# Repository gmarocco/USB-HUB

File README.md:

# USB Hub · microSD Reader · USB-UART — V2

A compact USB 2.0 Hi-Speed expansion board. A single USB Type-C upstream connection provides **four USB Type-A ports**, a **microSD card reader** and a **USB-to-UART bridge** with a 10-pin header. Everything fits on a 90 × 55 mm four-layer PCB designed in KiCad 10.

## Features

- **USB Type-C upstream port**: USB 2.0, reversible, with 5.1 kΩ pull-downs on CC1/CC2 so any USB-C host or charger turns on VBUS
- **Two cascaded Microchip USB2514B hubs**: 4-port, USB 2.0 Hi-Speed (480 Mbit/s) controllers
- **4 × USB Type-A downstream ports** on two dual stacked connectors
- **1 spare downstream port** on the `AUX-P` / `AUX-N` pads
- **microSD card reader** based on the Genesys Logic GL823K, which works as a standard USB Mass Storage device with no driver needed
- **USB ⇄ UART bridge** based on the WCH CH340K, with `TXD`, `RXD`, `RTS`, `CTS`, `DTR`, 3.3 V and 5 V on a 2.54 mm header
- **Port power switching**: AP22966 load switches driven by the hub (default), or PTC resettable fuses (fuse variant)
- **Protection**:
  - common-mode filter with built-in ESD protection on every external USB data pair
  - TVS diodes on every power rail and on the UART lines
  - resettable fuses on the input and on the header supply pins
- **Status LEDs** for port power, UART bridge power and SD card activity

## Block diagram

USB topology:

```mermaid
flowchart LR
    USBC["USB-C upstream (J2)"] --> CMF["ECMF02 CM filter + ESD"]
    CMF --> HUB1["Hub 1 - USB2514B (U2)"]
    HUB1 -- "DN1" --> P1["USB-A port 1 (J1)"]
    HUB1 -- "DN2" --> P2["USB-A port 2 (J1)"]
    HUB1 -- "DN3" --> AUX["AUX-P / AUX-N pads"]
    HUB1 -- "DN4" --> HUB2["Hub 2 - USB2514B (U3)"]
    HUB2 -- "DN1" --> P3["USB-A port 3 (J3)"]
    HUB2 -- "DN2" --> P4["USB-A port 4 (J3)"]
    HUB2 -- "DN3" --> UART["CH340K USB-UART (U6)"] --> HDR["10-pin header (J4)"]
    HUB2 -- "DN4" --> SDR["GL823K card reader (U7)"] --> SD["microSD socket (J5)"]
```

## Circuit description

The full schematics are available as PDF files:

- [Main circuit schematics (default variant, with load switches)](production/USB%20HUB%20SD%20UART%20V2_%20%20main%20circuit%20schematics.pdf)
- [Fuse variant circuit schematics](production/USB%20HUB%20SD%20UART%20V2_%20fuse%20variant%20circuit%20schematics.pdf)

The KiCad schematic sheets are in the [`hardware/`](hardware/) folder:

| Sheet | File | Content |
|---|---|---|
| 1 | `alimentazione_e_schema_a_blocchi.kicad_sch` | Block diagram, USB-C input, protection, 3.3 V LDO |
| 2 | `USB HUB SD v2.kicad_sch` | Two USB2514B hubs, port power switching, USB-A connectors |
| 3 | `ch349g.kicad_sch` | CH340K USB-UART bridge and UART header |
| 4 | `adattatori.kicad_sch` | Auxiliary parts: FT232RL and MIC2026 (not fitted), EMI7–EMI9, fiducials |
| 5 | `sd_card.kicad_sch` | GL823K card reader and microSD socket |

### Power input and protection (sheet 1)

- **J2** (Amphenol 12402012E212A) is a USB 2.0 Type-C receptacle. The D+/D− contacts of both rows are tied together, so the cable works in either orientation.
- **R25 and R27** (5.1 kΩ) pull CC1 and CC2 down, so the board is seen as a sink. The board does not negotiate USB Power Delivery.
- **Connector shield**: tied to GND through R26 (1 MΩ) in parallel with C25 (10 nF / 1 kV).
- **VBUS** goes through **F7** (Littelfuse 1206L150THWR PTC resettable fuse, 1.5 A hold) to make the **+5 V** rail. **D13** (SMBJ5.0A TVS) clamps transients on +5 V.
- **Upstream data pair**: filtered by **EMI6** (ST ECMF02-2AMX6, a common-mode filter with built-in ESD protection).
- **U1** (onsemi NCP1117ST33T3G LDO) makes the **+3.3 V** rail from +5 V. The 3.3 V rail is split by two 0 Ω links:
  - R28 feeds **+3V3_HUB** (the two USB2514B controllers).
  - R30 feeds **+3V3_CH340** (the CH340K and the 3.3 V pin of the UART header).

  The links let you isolate either load or measure its current.

### USB hub (sheet 2)

Two **USB2514B-I/M2** controllers (U2, U3) are connected in cascade. Each one has:

- a 24 MHz crystal (Epson TSX-3225, Y1/Y2) with 18 pF load capacitors
- a 12 kΩ RBIAS resistor
- 12 kΩ strap resistors on `CFG_SEL0`, `CFG_SEL1` and `NON_REM`, which select the hardware default configuration, so no EEPROM or SMBus setup is needed
- local decoupling on every 3.3 V supply pin

| Hub | Downstream port | Destination |
|---|---|---|
| U2 (hub 1) | DN1 | J1, port 1 (via EMI2) |
| U2 (hub 1) | DN2 | J1, port 2 (via EMI3) |
| U2 (hub 1) | DN3 | `AUX-P` / `AUX-N` pads (data lines only) |
| U2 (hub 1) | DN4 | Upstream port of U3 (via R12/R13, 0 Ω) |
| U3 (hub 2) | DN1 | J3, port 3 (via EMI4) |
| U3 (hub 2) | DN2 | J3, port 4 (via EMI5) |
| U3 (hub 2) | DN3 | CH340K USB-UART bridge (via R35/R36, 0 Ω) |
| U3 (hub 2) | DN4 | GL823K card reader (via R37/R38, 0 Ω) |

The external ports use two **Molex 67298-4091** dual stacked USB Type-A receptacles (J1, J3). Each port has:

- an **ECMF02-2AMX6** common-mode filter with ESD protection on D+/D−
- an **SMBJ5.0A** TVS on its VBUS line (D15, D18, D19, D20)
- a **VBUS LED** (D3, D16, D14, D17)

The shields of both connectors go to GND through the same 1 MΩ ‖ 10 nF / 1 kV network as the USB-C connector.

### Downstream port power: two assembly variants

The PCB supports two ways of powering the USB-A ports. They are defined as KiCad variants of the same design.

| | **Default (load switch)** | **Fuse variant** (`fusibili porte USB`) |
|---|---|---|
| Port power device | **U10, U11** (Diodes AP22966DC8-7, dual-channel load switch) | **F2, F11, F3, F12** (Littelfuse 1206L150THWR PTC, 1.5 A hold) |
| Control | Hub `PRTPWR1`/`PRTPWR2` drive `EN1`/`EN2` through R17, R43, R39 and R46 (0 Ω) | None: the ports are always powered |
| Behaviour | The hub switches each port on and off. Capacitors on the soft-start (`SS`) pins limit inrush current at turn-on | Each port has its own resettable overcurrent protection |
| Parts not fitted | F2, F3, F11, F12 | U10, U11 and their support parts |

### USB-UART bridge (sheet 3)

- **U6** is a **WCH CH340K**, which has a built-in oscillator. It runs from **+3V3_CH340** (`VCC` and `V3` tied together), so **all UART signals use 3.3 V logic levels**.
- **D4–D8** (Littelfuse SP4020-01FTG-C TVS) protect each UART line.
- The header supply pins are protected by PTC fuses (F4 for 3.3 V, F5 for 5 V) and SMBJ5.0A TVS diodes (D10, D11).
- **D12** shows that the bridge is powered.

**J4 – 2.54 mm 1×10 header pinout**

| Pin | Signal | Notes |
|---|---|---|
| 1 | +3V3 | From +3V3_CH340 through F4 (PTC) |
| 2 | DTR# | Output |
| 3 | GND | |
| 4 | RTS# | Output |
| 5 | CTS# | Input |
| 6 | GND | |
| 7 | TXD | CH340K transmit (connect to the target's RX) |
| 8 | RXD | CH340K receive (connect to the target's TX) |
| 9 | GND | |
| 10 | +5V | From +5 V through F5 (PTC) |

> **Note:** the 3.3 V header pin shares the NCP1117 LDO with the hub controllers. To power larger loads, use the 5 V pin.

### microSD card reader (sheet 5)

- **U7** is a **Genesys Logic GL823K**, a USB 2.0 SD card reader controller. It runs from +5 V and makes its own 3.3 V supply internally (decoupled by C21 and C22), and needs no external crystal.
- The card supply (`SUPPLY_CARD`) comes from the controller's internal power switch (`PMOS` pin).
- The 4-bit SD bus (`CLK`, `CMD`, `D0`–`D3`) goes directly to **J5**, a microSD socket (MSD-4-A).
- **D9** is the card activity LED (GL823K `LED` pin).
- The socket's card-detect switch is available on test point **TP3**.

### Indicators and test points

| Ref | Function |
|---|---|
| D3, D16 | VBUS present on J1 ports 1 and 2 |
| D14, D17 | VBUS present on J3 ports 3 and 4 |
| D12 | CH340K powered (+3V3_CH340) |
| D9 | microSD activity |
| TP2 | VBUS from USB-C, before fuse F7 |
| TP59 | +5 V rail, after fuse F7 |
| TP3 | microSD card-detect switch |
| AUX-P / AUX-N | D+ / D− of the spare hub port (U2 DN3) |

## Main components

| Ref | Part | Function |
|---|---|---|
| U2, U3 | Microchip USB2514B-I/M2 | 4-port USB 2.0 Hi-Speed hub controller |
| U6 | WCH CH340K | USB ⇄ UART bridge |
| U7 | Genesys Logic GL823K | USB 2.0 SD/microSD card reader controller |
| U1 | onsemi NCP1117ST33T3G | 3.3 V LDO regulator |
| U10, U11 | Diodes AP22966DC8-7 | Dual-channel load switch for port VBUS (default variant) |
| F2, F3, F11, F12 | Littelfuse 1206L150THWR | Port VBUS PTC fuses (fuse variant) |
| F4, F5, F7 | Littelfuse 1206L150THWR | Input and header PTC fuses |
| EMI2–EMI6 | ST ECMF02-2AMX6 | Common-mode filter + ESD protection for USB data lines |
| D4–D8 | Littelfuse SP4020-01FTG-C | ESD TVS on UART lines |
| D10, D11, D13, D15, D18–D20 | Vishay SMBJ5.0A-E3/52 | 600 W TVS on supply rails |
| J2 | Amphenol 12402012E212A | USB Type-C receptacle (upstream) |
| J1, J3 | Molex 67298-4091 | Dual stacked USB Type-A receptacle |
| J5 | MSD-4-A | microSD socket |
| J4 | 2.54 mm 1×10 header | UART + supply header |
| Y1, Y2 | Epson TSX-3225 24.0000 MHz | Hub reference crystals |

The complete bill of materials is in [`BOM_USB_HUB_SD v2.xlsx`](production/BOM_USB_HUB_SD%20v2.xlsx). An interactive HTML BOM, handy during assembly, is in [`USB_HUB v2 ibom.html`](production/USB_HUB%20v2%20ibom.html): download it and open it in a web browser.

## PCB

| Parameter | Value |
|---|---|
| Layers | 4 (F.Cu, In1.Cu, In2.Cu, B.Cu) |
| Board size | 90.4 × 55.5 mm, rounded corners |
| Upstream connector | USB Type-C (USB 2.0) |
| Downstream connectors | 2 × dual stacked USB Type-A, 1 × microSD, 1 × 10-pin 2.54 mm header |
| Supply | Bus-powered, 5 V from the upstream VBUS |
| EDA tool | KiCad 10.0 |

The PCB layer plots are in [`USB HUB SD v2 layer plot.pdf`](production/USB%20HUB%20SD%20v2%20layer%20plot.pdf).

## Repository contents

```text
USB-HUB/
├── README.md
├── docs/           Pictures used in this README
├── hardware/       KiCad 10 project: schematics, PCB, 3D models
│   └── lib/        Project symbol and footprint library
└── production/     Gerbers, BOM and PDF documentation
```

| Path | Description |
|---|---|
| `hardware/USB HUB SD v2.kicad_pro` | KiCad 10 project file |
| `hardware/USB HUB SD v2.kicad_sch` and sub-sheets | Hierarchical schematic (see the sheet table above) |
| `hardware/USB HUB SD v2.kicad_pcb` | PCB layout |
| `hardware/HUB USB v2.step`, `hardware/hub_USB.glb` | 3D models of the assembled board |
| `hardware/fabrication-toolkit-options.json` | Settings for the KiCad Fabrication Toolkit plugin |
| `hardware/sym-lib-table`, `hardware/fp-lib-table` | Project library tables |
| `hardware/lib/USB-HUB.kicad_sym` | Project symbol library |
| `hardware/lib/USB-HUB.pretty/` | Project footprint library |
| `production/gerber USB_HUB_SD_UART_V2.zip` | Gerber manufacturing files |
| `production/BOM_USB_HUB_SD v2.xlsx` | Bill of materials |
| `production/USB_HUB v2 ibom.html` | Interactive HTML BOM |
| `production/*.pdf` | Schematics (both variants) and PCB layer plots |
| `docs/` | Pictures used in this README |

The Fabrication Toolkit plugin writes its output to `hardware/production/`, which git ignores. The released manufacturing files are the ones in `production/` at the repository root.

## Usage

1. Connect the USB-C port to a computer with a USB-C cable, or with a USB-A to USB-C cable.
2. The operating system finds two USB hubs, a **CH340 serial port**, and a **USB Mass Storage** device for the microSD reader.
3. The CH340 driver is built into Linux and macOS. Windows usually installs it automatically through Windows Update; if it doesn't, download it from the WCH website.
4. Plug USB devices into the four Type-A ports. They all share the 5 V supply from the upstream port.

> **Power budget:** the board does not negotiate USB Power Delivery. The total current available to all ports is limited by the host port or power source and by the input PTC fuse F7 (1.5 A hold current).

## Author

Designed by **Gabriele Marocco**, [PCB Semplice](https://pcbsemplice.com).

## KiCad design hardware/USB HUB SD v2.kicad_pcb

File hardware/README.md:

# USB Hub · microSD Reader · USB-UART — V2

A compact USB 2.0 Hi-Speed expansion board. A single USB Type-C upstream connection provides **four USB Type-A ports**, a **microSD card reader** and a **USB-to-UART bridge** with a 10-pin header. Everything fits on a 90 × 55 mm four-layer PCB designed in KiCad 10.

## Features

- **USB Type-C upstream port**: USB 2.0, reversible, with 5.1 kΩ pull-downs on CC1/CC2 so any USB-C host or charger turns on VBUS
- **Two cascaded Microchip USB2514B hubs**: 4-port, USB 2.0 Hi-Speed (480 Mbit/s) controllers
- **4 × USB Type-A downstream ports** on two dual stacked connectors
- **1 spare downstream port** on the `AUX-P` / `AUX-N` pads
- **microSD card reader** based on the Genesys Logic GL823K, which works as a standard USB Mass Storage device with no driver needed
- **USB ⇄ UART bridge** based on the WCH CH340K, with `TXD`, `RXD`, `RTS`, `CTS`, `DTR`, 3.3 V and 5 V on a 2.54 mm header
- **Port power switching**: AP22966 load switches driven by the hub (default), or PTC resettable fuses (fuse variant)
- **Protection**:
  - common-mode filter with built-in ESD protection on every external USB data pair
  - TVS diodes on every power rail and on the UART lines
  - resettable fuses on the input and on the header supply pins
- **Status LEDs** for port power, UART bridge power and SD card activity

## Block diagram

USB topology:

```mermaid
flowchart LR
    USBC["USB-C upstream (J2)"] --> CMF["ECMF02 CM filter + ESD"]
    CMF --> HUB1["Hub 1 - USB2514B (U2)"]
    HUB1 -- "DN1" --> P1["USB-A port 1 (J1)"]
    HUB1 -- "DN2" --> P2["USB-A port 2 (J1)"]
    HUB1 -- "DN3" --> AUX["AUX-P / AUX-N pads"]
    HUB1 -- "DN4" --> HUB2["Hub 2 - USB2514B (U3)"]
    HUB2 -- "DN1" --> P3["USB-A port 3 (J3)"]
    HUB2 -- "DN2" --> P4["USB-A port 4 (J3)"]
    HUB2 -- "DN3" --> UART["CH340K USB-UART (U6)"] --> HDR["10-pin header (J4)"]
    HUB2 -- "DN4" --> SDR["GL823K card reader (U7)"] --> SD["microSD socket (J5)"]
```

## Circuit description

The full schematics are available as PDF files:

- [Main circuit schematics (default variant, with load switches)](gerber-%20documentation/USB%20HUB%20SD%20UART%20V2_%20%20main%20circuit%20schematics.pdf)
- [Fuse variant circuit schematics](gerber-%20documentation/USB%20HUB%20SD%20UART%20V2_%20fuse%20variant%20circuit%20schematics.pdf)

| Sheet | File | Content |
|---|---|---|
| 1 | `alimentazione_e_schema_a_blocchi.kicad_sch` | Block diagram, USB-C input, protection, 3.3 V LDO |
| 2 | `USB HUB SD v2.kicad_sch` | Two USB2514B hubs, port power switching, USB-A connectors |
| 3 | `ch349g.kicad_sch` | CH340K USB-UART bridge and UART header |
| 4 | `adattatori.kicad_sch` | Auxiliary parts: FT232RL and MIC2026 (not fitted), EMI7–EMI9, fiducials |
| 5 | `sd_card.kicad_sch` | GL823K card reader and microSD socket |

### Power input and protection (sheet 1)

- **J2** (Amphenol 12402012E212A) is a USB 2.0 Type-C receptacle. The D+/D− contacts of both rows are tied together, so the cable works in either orientation.
- **R25 and R27** (5.1 kΩ) pull CC1 and CC2 down, so the board is seen as a sink. The board does not negotiate USB Power Delivery.
- **Connector shield**: tied to GND through R26 (1 MΩ) in parallel with C25 (10 nF / 1 kV).
- **VBUS** goes through **F7** (Littelfuse 1206L150THWR PTC resettable fuse, 1.5 A hold) to make the **+5 V** rail. **D13** (SMBJ5.0A TVS) clamps transients on +5 V.
- **Upstream data pair**: filtered by **EMI6** (ST ECMF02-2AMX6, a common-mode filter with built-in ESD protection).
- **U1** (onsemi NCP1117ST33T3G LDO) makes the **+3.3 V** rail from +5 V. The 3.3 V rail is split by two 0 Ω links:
  - R28 feeds **+3V3_HUB** (the two USB2514B controllers).
  - R30 feeds **+3V3_CH340** (the CH340K and the 3.3 V pin of the UART header).

  The links let you isolate either load or measure its current.

### USB hub (sheet 2)

Two **USB2514B-I/M2** controllers (U2, U3) are connected in cascade. Each one has:

- a 24 MHz crystal (Epson TSX-3225, Y1/Y2) with 18 pF load capacitors
- a 12 kΩ RBIAS resistor
- 12 kΩ strap resistors on `CFG_SEL0`, `CFG_SEL1` and `NON_REM`, which select the hardware default configuration, so no EEPROM or SMBus setup is needed
- local decoupling on every 3.3 V supply pin

| Hub | Downstream port | Destination |
|---|---|---|
| U2 (hub 1) | DN1 | J1, port 1 (via EMI2) |
| U2 (hub 1) | DN2 | J1, port 2 (via EMI3) |
| U2 (hub 1) | DN3 | `AUX-P` / `AUX-N` pads (data lines only) |
| U2 (hub 1) | DN4 | Upstream port of U3 (via R12/R13, 0 Ω) |
| U3 (hub 2) | DN1 | J3, port 3 (via EMI4) |
| U3 (hub 2) | DN2 | J3, port 4 (via EMI5) |
| U3 (hub 2) | DN3 | CH340K USB-UART bridge (via R35/R36, 0 Ω) |
| U3 (hub 2) | DN4 | GL823K card reader (via R37/R38, 0 Ω) |

The external ports use two **Molex 67298-4091** dual stacked USB Type-A receptacles (J1, J3). Each port has:

- an **ECMF02-2AMX6** common-mode filter with ESD protection on D+/D−
- an **SMBJ5.0A** TVS on its VBUS line (D15, D18, D19, D20)
- a **VBUS LED** (D3, D16, D14, D17)

The shields of both connectors go to GND through the same 1 MΩ ‖ 10 nF / 1 kV network as the USB-C connector.

### Downstream port power: two assembly variants

The PCB supports two ways of powering the USB-A ports. They are defined as KiCad variants of the same design.

| | **Default (load switch)** | **Fuse variant** (`fusibili porte USB`) |
|---|---|---|
| Port power device | **U10, U11** (Diodes AP22966DC8-7, dual-channel load switch) | **F2, F11, F3, F12** (Littelfuse 1206L150THWR PTC, 1.5 A hold) |
| Control | Hub `PRTPWR1`/`PRTPWR2` drive `EN1`/`EN2` through R17, R43, R39 and R46 (0 Ω) | None: the ports are always powered |
| Behaviour | The hub switches each port on and off. Capacitors on the soft-start (`SS`) pins limit inrush current at turn-on | Each port has its own resettable overcurrent protection |
| Parts not fitted | F2, F3, F11, F12 | U10, U11 and their support parts |

### USB-UART bridge (sheet 3)

- **U6** is a **WCH CH340K**, which has a built-in oscillator. It runs from **+3V3_CH340** (`VCC` and `V3` tied together), so **all UART signals use 3.3 V logic levels**.
- **D4–D8** (Littelfuse SP4020-01FTG-C TVS) protect each UART line.
- The header supply pins are protected by PTC fuses (F4 for 3.3 V, F5 for 5 V) and SMBJ5.0A TVS diodes (D10, D11).
- **D12** shows that the bridge is powered.

**J4 – 2.54 mm 1×10 header pinout**

| Pin | Signal | Notes |
|---|---|---|
| 1 | +3V3 | From +3V3_CH340 through F4 (PTC) |
| 2 | DTR# | Output |
| 3 | GND | |
| 4 | RTS# | Output |
| 5 | CTS# | Input |
| 6 | GND | |
| 7 | TXD | CH340K transmit (connect to the target's RX) |
| 8 | RXD | CH340K receive (connect to the target's TX) |
| 9 | GND | |
| 10 | +5V | From +5 V through F5 (PTC) |

> **Note:** the 3.3 V header pin shares the NCP1117 LDO with the hub controllers. To power larger loads, use the 5 V pin.

### microSD card reader (sheet 5)

- **U7** is a **Genesys Logic GL823K**, a USB 2.0 SD card reader controller. It runs from +5 V and makes its own 3.3 V supply internally (decoupled by C21 and C22), and needs no external crystal.
- The card supply (`SUPPLY_CARD`) comes from the controller's internal power switch (`PMOS` pin).
- The 4-bit SD bus (`CLK`, `CMD`, `D0`–`D3`) goes directly to **J5**, a microSD socket (MSD-4-A).
- **D9** is the card activity LED (GL823K `LED` pin).
- The socket's card-detect switch is available on test point **TP3**.

### Indicators and test points

| Ref | Function |
|---|---|
| D3, D16 | VBUS present on J1 ports 1 and 2 |
| D14, D17 | VBUS present on J3 ports 3 and 4 |
| D12 | CH340K powered (+3V3_CH340) |
| D9 | microSD activity |
| TP2 | VBUS from USB-C, before fuse F7 |
| TP59 | +5 V rail, after fuse F7 |
| TP3 | microSD card-detect switch |
| AUX-P / AUX-N | D+ / D− of the spare hub port (U2 DN3) |

## Main components

| Ref | Part | Function |
|---|---|---|
| U2, U3 | Microchip USB2514B-I/M2 | 4-port USB 2.0 Hi-Speed hub controller |
| U6 | WCH CH340K | USB ⇄ UART bridge |
| U7 | Genesys Logic GL823K | USB 2.0 SD/microSD card reader controller |
| U1 | onsemi NCP1117ST33T3G | 3.3 V LDO regulator |
| U10, U11 | Diodes AP22966DC8-7 | Dual-channel load switch for port VBUS (default variant) |
| F2, F3, F11, F12 | Littelfuse 1206L150THWR | Port VBUS PTC fuses (fuse variant) |
| F4, F5, F7 | Littelfuse 1206L150THWR | Input and header PTC fuses |
| EMI2–EMI6 | ST ECMF02-2AMX6 | Common-mode filter + ESD protection for USB data lines |
| D4–D8 | Littelfuse SP4020-01FTG-C | ESD TVS on UART lines |
| D10, D11, D13, D15, D18–D20 | Vishay SMBJ5.0A-E3/52 | 600 W TVS on supply rails |
| J2 | Amphenol 12402012E212A | USB Type-C receptacle (upstream) |
| J1, J3 | Molex 67298-4091 | Dual stacked USB Type-A receptacle |
| J5 | MSD-4-A | microSD socket |
| J4 | 2.54 mm 1×10 header | UART + supply header |
| Y1, Y2 | Epson TSX-3225 24.0000 MHz | Hub reference crystals |

The complete bill of materials is in [`BOM_USB_HUB_SD v2.xlsx`](gerber-%20documentation/BOM_USB_HUB_SD%20v2.xlsx).

## PCB

| Parameter | Value |
|---|---|
| Layers | 4 (F.Cu, In1.Cu, In2.Cu, B.Cu) |
| Board size | 90.4 × 55.5 mm, rounded corners |
| Upstream connector | USB Type-C (USB 2.0) |
| Downstream connectors | 2 × dual stacked USB Type-A, 1 × microSD, 1 × 10-pin 2.54 mm header |
| Supply | Bus-powered, 5 V from the upstream VBUS |
| EDA tool | KiCad 10.0 |

The PCB layer plots are in [`USB HUB SD v2 layer plot.pdf`](gerber-%20documentation/USB%20HUB%20SD%20v2%20layer%20plot.pdf).

## Repository contents

| Path | Description |
|---|---|
| `USB HUB SD v2.kicad_pro` | KiCad 10 project file |
| `USB HUB SD v2.kicad_sch` and sub-sheets | Hierarchical schematic (see the sheet table above) |
| `USB HUB SD v2.kicad_pcb` | PCB layout |
| `HUB USB v2.step`, `hub_USB.glb` | 3D models of the assembled board |
| `fabrication-toolkit-options.json` | Settings for the KiCad Fabrication Toolkit plugin |
| `gerber- documentation/gerber USB_HUB_SD_UART_V2.zip` | Gerber manufacturing files |
| `gerber- documentation/BOM_USB_HUB_SD v2.xlsx` | Bill of materials |
| `gerber- documentation/*.pdf` | Schematics (both variants) and PCB layer plots |
| `images/` | Pictures used in this README |

## Usage

1. Connect the USB-C port to a computer with a USB-C cable, or with a USB-A to USB-C cable.
2. The operating system finds two USB hubs, a **CH340 serial port**, and a **USB Mass Storage** device for the microSD reader.
3. The CH340 driver is built into Linux and macOS. Windows usually installs it automatically through Windows Update; if it doesn't, download it from the WCH website.
4. Plug USB devices into the four Type-A ports. They all share the 5 V supply from the upstream port.

> **Power budget:** the board does not negotiate USB Power Delivery. The total current available to all ports is limited by the host port or power source and by the input PTC fuse F7 (1.5 A hold current).

## Author

Designed by **Gabriele Marocco**, [PCB Semplice](https://pcbsemplice.com).

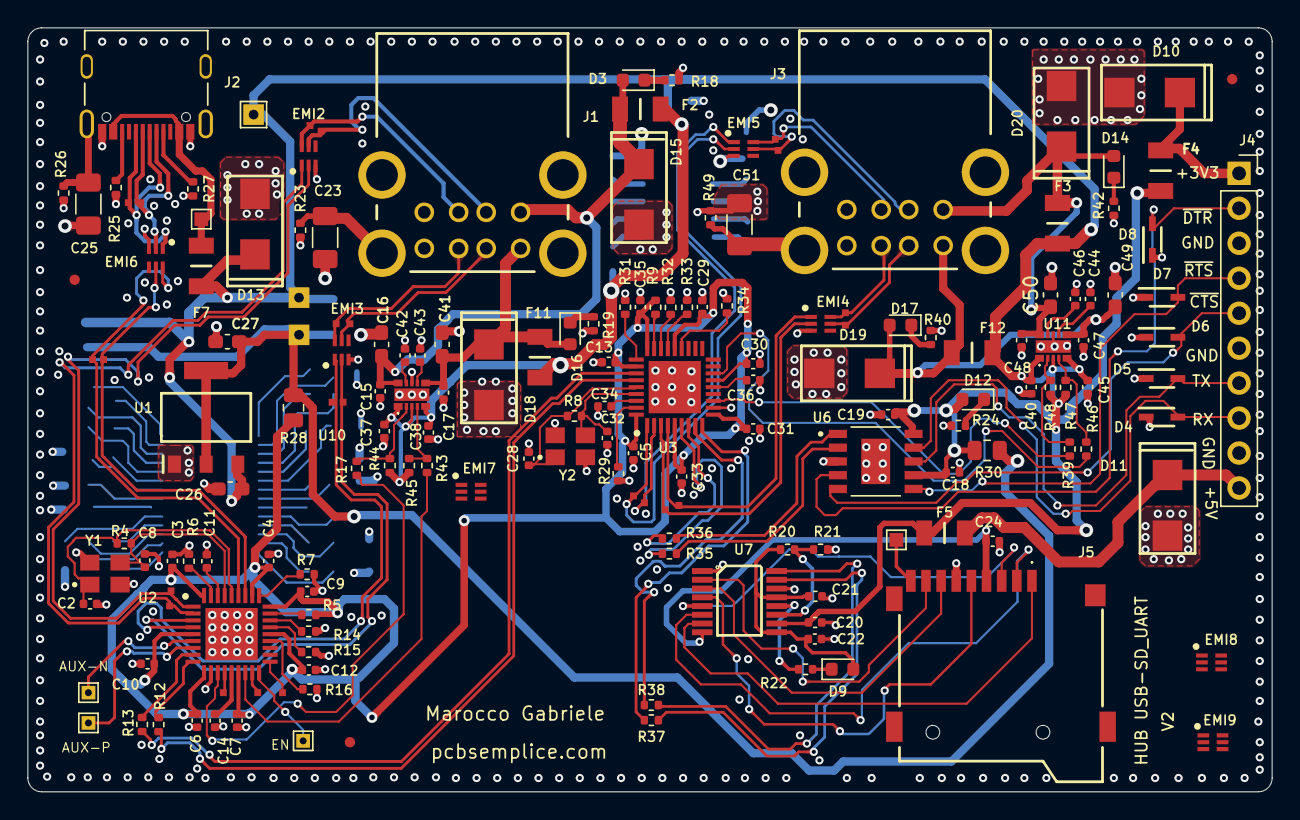
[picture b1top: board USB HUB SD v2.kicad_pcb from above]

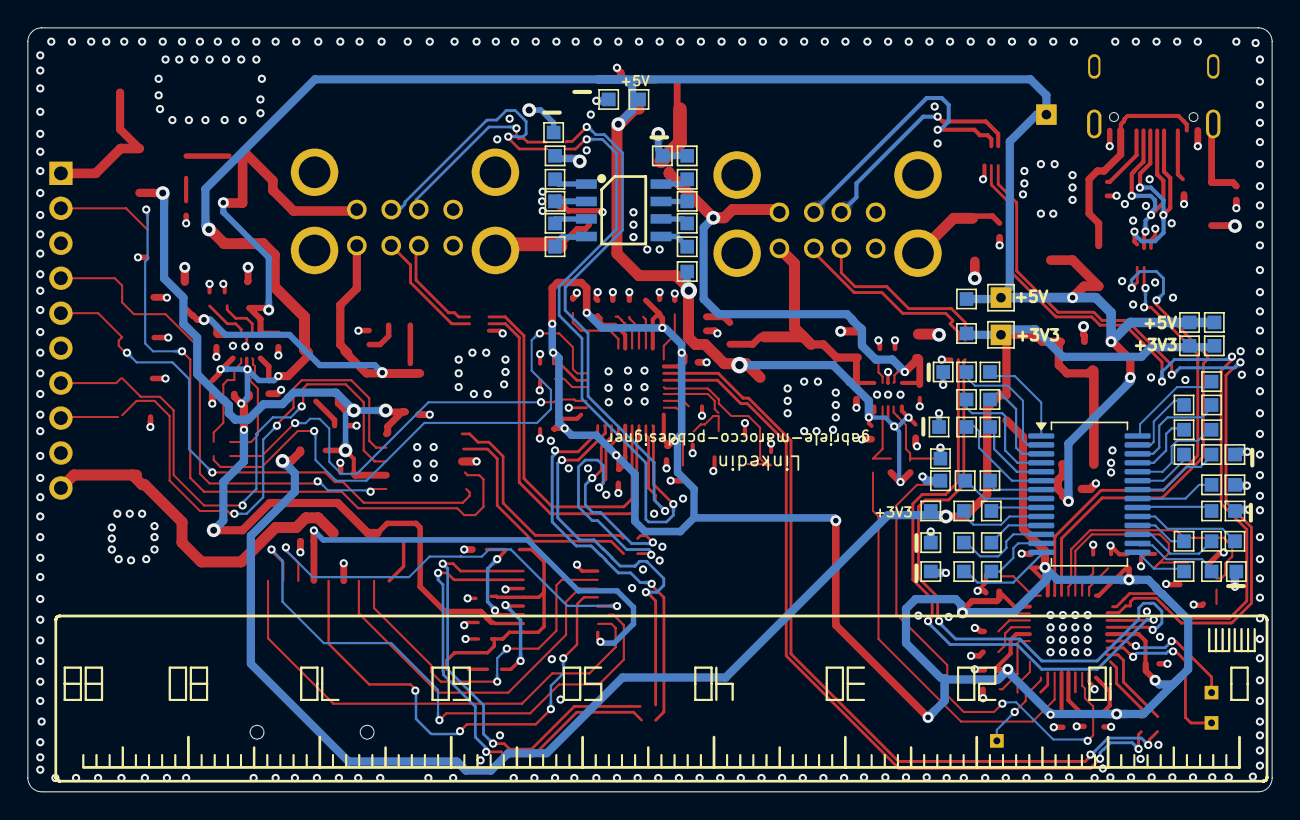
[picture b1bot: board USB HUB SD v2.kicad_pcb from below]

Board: 4 copper layers, 90.4 x 55.5 mm, 235 parts (64 on the bottom side), 145 nets.

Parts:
C2, C8, C28, C32: 18p 50V 0402; C_0402_1005Metric
C3, C5, C11, C14, C21, C34, C36: 4u7 16V 0402; C_0402_1005Metric
C4, C6, C7, C9, C10, C12, C13, C15, C17, C18, C19, C20, C22, C24, C29, C30, C31, C33, C35, C47, C48: 100n 50V 0402; C_0402_1005Metric
C16, C26, C27, C41, C49, C50: 10u 16V 0603; C_0603_1608Metric_Pad1.08x0.95mm_HandSolder
C23, C25, C51: 10n 1kV 1206; C_1206_3216Metric_Pad1.33x1.80mm_HandSolder
C37, C38, C40, C45: 1u 16V 0402; C_0402_1005Metric
C42, C43, C44, C46: 1n 50V 0402; C_0402_1005Metric
D3, D9, D12, D14, D16, D17: LED 0603; LED_0603_1608Metric
D4, D5, D6, D7, D8: SP4020-01FTG-C; SOD2613X114N
D10, D11, D13, D15, D18, D19, D20: SMBJ5.0A-E3_52; DIOM5436X244N
EMI2, EMI3, EMI4, EMI5, EMI6, EMI7, EMI8, EMI9: ECMF02-2AMX6; SON50P150X170X55-6N-D
F2, F3, F4, F5, F7, F11, F12: 1206L150THWR; FUSC3216X100N
FTG1, FTG2, FTG3: Use only in PCB; Fiducial_0.75mm_Mask1.5mm
J1, J3: 67298-4091; 672984091
J2: 12402012E212A; AMPHENOL_12402012E212A
J4: PM2.54-1*10; PinSocket_1x10_P2.54mm_Vertical
J5: MSD-4-A; MSD4A
R4, R8, R23, R26, R49: 1M 0402; R_0402_1005Metric
R5, R6, R7, R9, R14, R15, R16, R20, R21, R29, R31, R32, R33, R34, R44, R45, R47, R48: 12k 0402; R_0402_1005Metric
R12, R13, R17, R35, R36, R37, R38, R39, R43, R46: 0R 0402; R_0402_1005Metric
R18, R19, R22, R24, R40, R42: 1k 0402; R_0402_1005Metric
R25, R27: 5K1 0402; R_0402_1005Metric
R28, R30: 0R 0805; R_0805_2012Metric
TP2, TP3, TP5, TP6, TP7, TP8, TP9, TP10, TP11, TP12, TP13, TP14, TP15, TP16, TP17, TP18, TP19, TP20, TP21, TP22, TP23, TP24, TP25, TP26, TP27, TP28, TP29, TP30, TP31, TP32, TP33, TP34, TP35, TP36, TP37, TP38, TP39, TP40, TP41, TP42, TP43, TP44, TP46, TP48, TP49, TP50, TP51, TP52, TP53, TP54, TP55, TP56, TP57, TP58, TP61, TP62, TP64, TP65, TP66, TP67, TP68, TP70: TestPoint; TestPoint_Pad_1.0x1.0mm
TP45, TP47, TP59: TestPoint; TestPoint_THTPad_1.5x1.5mm_Drill0.7mm
TP60, TP63, TP71, TP72, TP73, TP74, TP75, TP76, TP79, TP81, TP82, TP83, TP84, TP85, TP86, TP87, TP88, TP89, TP90, TP91, TP92, TP93, TP94: TestPoint; TestPoint_Pad_D0.5mm
TP77, TP78, TP80: TestPoint; TestPoint_THTPad_1.0x1.0mm_Drill0.5mm
U1: NCP1117ST33T3G; SOT230P700X180-4N
U2, U3: USB2514BT-I_M2; QFN50P600X600X100-37N-D
U6: CH340K; SOP100P600X160-11N
U7: GL823K; SOP64P600X175-16N
U8: FT232RL; SSOP-28_5.3x10.2mm_P0.65mm
U9: MIC2026-1YM-TR; SOIC127P600X163-8N
U10, U11: AP22966DC8-7; AP22966DC87
Y1, Y2: TSX-3225_24.0000MF20G-AC3; TSX-3225

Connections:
+3V3: C27.1, R28.2, R30.2, TP47.1 (1_1), TP48.1 (1_1), TP49.1 (1_1), TP50.1 (1_1), TP70.1 (1_1), U1.2 (OUTPUT_1), U1.4 (OUTPUT_2)
+3V3_CH340: C18.1, C19.1, D12.2 (A), F4.1, R30.1, U6.7 (VCC), U6.10 (V3)
+3V3_HUB: C3.1, C4.1, C5.1, C6.1, C7.1, C9.1, C10.1, C12.1, C13.1, C29.1, C30.1, C31.1, C33.1, C35.1, R5.1, R9.1, R28.1, U2.5 (VDDA33_1), U2.10 (VDDA33_2), U2.15 (VDD33_1), U2.23 (VDD33_2), U2.27 (VBUS_DET), U2.29 (VDDA33_3), U2.36 (VDDA33_4), U3.5 (VDDA33_1), U3.10 (VDDA33_2), U3.15 (VDD33_1), U3.23 (VDD33_2), U3.27 (VBUS_DET), U3.29 (VDDA33_3), U3.36 (VDDA33_4)
+5V: C20.1, C26.1, C37.1, C38.1, C40.1, C45.1, D13.1 (K), F2.1, F3.1, F5.1, F7.2, F11.1, F12.1, R44.1, R45.2, R47.2, R48.1, TP43.1 (1_1), TP44.1 (1_1), TP45.1 (1_1), TP46.1 (1_1), TP59.1 (1_1), TP67.1 (1_1), TP68.1 (1_1), U1.3 (INPUT), U7.10 (5V), U10.1 (VIN1), U10.3 (VBIAS), U10.5 (VIN2), U11.1 (VIN1), U11.3 (VBIAS), U11.5 (VIN2)
/Alimentazione e schema a blocchi/+5V_IN: F7.1, J2.A4_B9 (VBUS), J2.B4_A9 (VBUS), TP2.1 (1_1)
/Alimentazione e schema a blocchi/USBINC_N: EMI6.2 (D_2), J2.A7 (D-_A), J2.B7 (D-_B), TP89.1 (1_1)
/Alimentazione e schema a blocchi/USBINC_P: EMI6.1 (D_1), J2.A6 (D+_A), J2.B6 (D+_B), TP90.1 (1_1)
/CH349G/RXD: D4.2, J4.8, U6.9 (RXD)
/CH349G/TXD: D5.2, J4.7, U6.8 (TXD)
/CH349G/~CTS: D6.2, J4.5, U6.5 (~CTS)
/CH349G/~DTR: D8.2, J4.2, U6.4 (~DTR)
/CH349G/~RTS: D7.2, J4.4, U6.6 (~RTS)
/SD CARD/CLK: J5.5 (CLK), U7.4 (CLK)
/SD CARD/CMD: J5.3 (CMD), U7.5 (CMD)
/SD CARD/D0: J5.7 (DAT0), U7.3 (D0)
/SD CARD/D1: J5.8 (DAT1), U7.2 (D1)
/SD CARD/D2: J5.1 (DAT2), U7.7 (D2)
/SD CARD/D3: J5.2 (CD/DAT3), U7.6 (D3)
/SD CARD/SUPPLY_CARD: C24.1, J5.4 (VDD), U7.8 (PMOS)
/USB HUB SD v2/+5V_out1: C15.1, C16.1, D3.2 (A), D15.1 (K), F2.2, J1.A1 (VCC1), U10.10 (VOUT1)
/USB HUB SD v2/+5V_out2: C17.1, C41.1, D16.2 (A), D18.1 (K), F11.2, J1.B1 (VCC2), U10.6 (VOUT2)
/USB HUB SD v2/+5V_out3: C48.1, C50.1, D14.2 (A), D20.1 (K), F3.2, J3.A1 (VCC1), U11.10 (VOUT1)
/USB HUB SD v2/+5V_out4: C47.1, C49.1, D17.2 (A), D19.1 (K), F12.2, J3.B1 (VCC2), U11.6 (VOUT2)
/USB HUB SD v2/SD_N: R38.2, U3.8 (USBDM_DN4/PRT_DIS_M4)
/USB HUB SD v2/SD_P: R37.2, U3.9 (USBDP_DN4/PRT_DIS_P4)
/USB HUB SD v2/UART_N: R35.2, U3.6 (USBDM_DN3/PRT_DIS_M3)
/USB HUB SD v2/UART_P: R36.2, U3.7 (USBDP_DN3/PRT_DIS_P3)
/USB HUB SD v2/USB1C_N: EMI2.5 (D-), J1.A2 (DM1), TP71.1 (1_1)
/USB HUB SD v2/USB1C_P: EMI2.6 (D+), J1.A3 (DP1), TP72.1 (1_1)
/USB HUB SD v2/USB1F_N: EMI2.2 (D_2), TP60.1 (1_1), U2.1 (USBDM_DN1/PRT_DIS_M1)
/USB HUB SD v2/USB1F_P: EMI2.1 (D_1), TP63.1 (1_1), U2.2 (USBDP_DN1/PRT_DIS_P1)
/USB HUB SD v2/USB2C_N: EMI3.5 (D-), J1.B2 (DM2), TP75.1 (1_1)
/USB HUB SD v2/USB2C_P: EMI3.6 (D+), J1.B3 (DP2), TP76.1 (1_1)
/USB HUB SD v2/USB2F_N: EMI3.2 (D_2), TP73.1 (1_1), U2.3 (USBDM_DN2/PRT_DIS_M2)
/USB HUB SD v2/USB2F_P: EMI3.1 (D_1), TP74.1 (1_1), U2.4 (USBDP_DN2/PRT_DIS_P2)
/USB HUB SD v2/USB3C_N: EMI5.5 (D-), J3.A2 (DM1), TP87.1 (1_1)
/USB HUB SD v2/USB3C_P: EMI5.6 (D+), J3.A3 (DP1), TP88.1 (1_1)
/USB HUB SD v2/USB3F_N: EMI5.2 (D_2), TP83.1 (1_1), U3.1 (USBDM_DN1/PRT_DIS_M1)
/USB HUB SD v2/USB3F_P: EMI5.1 (D_1), TP84.1 (1_1), U3.2 (USBDP_DN1/PRT_DIS_P1)
/USB HUB SD v2/USB4C_N: EMI4.5 (D-), J3.B2 (DM2), TP85.1 (1_1)
/USB HUB SD v2/USB4C_P: EMI4.6 (D+), J3.B3 (DP2), TP86.1 (1_1)
/USB HUB SD v2/USB4F_N: EMI4.2 (D_2), TP81.1 (1_1), U3.3 (USBDM_DN2/PRT_DIS_M2)
/USB HUB SD v2/USB4F_P: EMI4.1 (D_1), TP82.1 (1_1), U3.4 (USBDP_DN2/PRT_DIS_P2)
/USB HUB SD v2/USB4_N: R13.2, U2.8 (USBDM_DN4/PRT_DIS_M4)
/USB HUB SD v2/USB4_P: R12.2, U2.9 (USBDP_DN4/PRT_DIS_P4)
/USB HUB SD v2/USBAUX_N: TP77.1 (1_1), U2.6 (USBDM_DN3/PRT_DIS_M3)
/USB HUB SD v2/USBAUX_P: TP78.1 (1_1), U2.7 (USBDP_DN3/PRT_DIS_P3)
/USB HUB SD v2/USBOUT_N: R13.1, U3.30 (USBDM_UP)
/USB HUB SD v2/USBOUT_P: R12.1, U3.31 (USBDP_UP)
GND: C2.2, C3.2, C4.2, C5.2, C6.2, C7.2, C8.2, C9.2, C10.2, C11.2, C12.2, C13.2, C14.2, C15.2, C16.2, C17.2, C18.2, C19.2, C20.2, C21.2, C22.2, C23.2, C24.2, C25.2, C26.2, C27.2, C28.2, C29.2, C30.2, C31.2, C32.2, C33.2, C34.2, C35.2, C36.2, C37.2, C38.2, C40.2, C41.2, C42.2, C43.2, C44.2, C45.2, C46.2, C47.2, C48.2, C49.2, C50.2, C51.2, D4.1, D5.1, D6.1, D7.1, D8.1, D10.2 (A), D11.2 (A), D13.2 (A), D15.2 (A), D18.2 (A), D19.2 (A), D20.2 (A), EMI2.3 (GND), EMI3.3 (GND), EMI4.3 (GND), EMI5.3 (GND), EMI6.3 (GND), J1.A4 (GND1), J1.B4 (GND2), J2.A1_B12 (GND), J2.B1_A12 (GND), J3.A4 (GND1), J3.B4 (GND2), J4.3, J4.6, J4.9, J5.6 (VSS), R6.1, R7.1, R14.1, R15.1, R16.1, R18.1, R19.1, R21.1, R23.1, R24.1, R25.1, R26.1, R27.2, R29.1, R31.1, R32.1, R33.1, R34.1, R40.1, R42.1, R49.1, TP33.1 (1_1), TP34.1 (1_1), TP35.1 (1_1), TP36.1 (1_1), TP37.1 (1_1), TP38.1 (1_1), TP39.1 (1_1), TP40.1 (1_1), TP41.1 (1_1), TP42.1 (1_1), TP61.1 (1_1), TP62.1 (1_1), TP64.1 (1_1), TP65.1 (1_1), TP66.1 (1_1), U1.1 (ADJ/GND), U2.11 (TEST), U2.37 (VSS), U3.11 (TEST), U3.37 (VSS), U6.0 (EXP(GND)), U6.3 (GND), U7.1 (VSS_1), U7.14 (VSS_2), U10.8 (GND), U10.11 (EP), U11.8 (GND), U11.11 (EP), Y1.2 (GND_1), Y1.4 (GND_2), Y2.2 (GND_1), Y2.4 (GND_2)
unnamed: C23.1, J1.MH4, R23.2
unnamed: C25.1, J2.SH2 (SHIELD), R26.2
unnamed: C51.1, J3.MH4, R49.2
unnamed: D3.1 (K), R18.2
unnamed: C21.1, C22.1, D9.2 (A), R20.1, U7.9 (VDD), U7.13 (VDDA)
unnamed: D9.1 (K), R22.2
unnamed: D10.1 (K), F4.2, J4.1
unnamed: D11.1 (K), F5.2, J4.10
unnamed: D12.1 (K), R24.2
unnamed: D14.1 (K), R42.2
unnamed: D16.1 (K), R19.2
unnamed: D17.1 (K), R40.2
unnamed: J2.A5 (CC1_A), R27.1
unnamed: J2.B5 (CC1_B), R25.2
unnamed: J5.CD1, TP3.1 (1_1)
unnamed: TP15.1 (1_1), U8.7 (GND)
unnamed: TP16.1 (1_1), U8.18 (GND)
unnamed: TP17.1 (1_1), U8.21 (GND)
unnamed: TP22.1 (1_1), U8.23 (CBUS0)
unnamed: TP32.1 (1_1), U8.8 (CBUS0)
unnamed: C14.1, U2.14 (CRFILT)
unnamed: R14.2, U2.25 (HS_IND/CFG_SEL1)
unnamed: TP93.1 (1_1), U2.13 (OCS_N1)
unnamed: TP94.1 (1_1), U2.17 (OCS_N2)
unnamed: TP79.1 (1_1), U2.19 (OCS_N3)
unnamed: C11.1, U2.34 (PLLFILT)
unnamed: R17.2, U2.12 (PRTPWR1/BC_EN1)
unnamed: R43.2, U2.16 (PRTPWR2/BC_EN2)
unnamed: TP80.1 (1_1), U2.18 (PRTPWR3/BC_EN3)
unnamed: R6.2, U2.35 (RBIAS)
unnamed: R15.2, U2.24 (SCL/SMBCLK/CFG_SEL0)
unnamed: R16.2, U2.22 (SDA/SMBDATA/NON_REM1)
unnamed: R7.2, U2.28 (SUSP_IND/)
unnamed: C8.1, R4.1, U2.33 (XTALIN/CLKIN), Y1.3
unnamed: C2.1, R4.2, U2.32 (XTALOUT), Y1.1
unnamed: R5.2, U2.26 (~RESET)
unnamed: C36.1, U3.14 (CRFILT)
unnamed: R32.2, U3.25 (HS_IND/CFG_SEL1)
unnamed: C34.1, U3.34 (PLLFILT)
unnamed: R39.2, U3.12 (PRTPWR1/BC_EN1)
unnamed: R46.2, U3.16 (PRTPWR2/BC_EN2)
unnamed: R29.2, U3.35 (RBIAS)
unnamed: R33.2, U3.24 (SCL/SMBCLK/CFG_SEL0)
unnamed: R34.2, U3.22 (SDA/SMBDATA/NON_REM1)
unnamed: R31.2, U3.28 (SUSP_IND/)
unnamed: C32.1, R8.1, U3.33 (XTALIN/CLKIN), Y2.3
unnamed: C28.1, R8.2, U3.32 (XTALOUT), Y2.1
unnamed: R9.2, U3.26 (~RESET)
unnamed: R20.2, R21.2, U7.11 (GPIO)
unnamed: R22.1, U7.12 (LED)
unnamed: TP7.1 (1_1), U8.17 (3V3OUT)
unnamed: TP31.1 (1_1), U8.24 (AGND2)
unnamed: TP14.1 (1_1), U8.25 (AGND)
unnamed: TP21.1 (1_1), U8.22 (CBUS1)
unnamed: TP20.1 (1_1), U8.13 (CBUS2)
unnamed: TP19.1 (1_1), U8.14 (CBUS3)
unnamed: TP18.1 (1_1), U8.12 (CBUS4)
unnamed: TP27.1 (1_1), U8.11 (CTS)
unnamed: TP24.1 (1_1), U8.10 (DCD)
unnamed: TP25.1 (1_1), U8.9 (DCR)
unnamed: TP26.1 (1_1), U8.2 (DTR)
unnamed: TP11.1 (1_1), U8.27 (OSCI)
unnamed: TP12.1 (1_1), U8.28 (OSCO)
unnamed: TP23.1 (1_1), U8.6 (RI)
unnamed: TP28.1 (1_1), U8.3 (RTS)
unnamed: TP29.1 (1_1), U8.5 (RXD)
unnamed: TP13.1 (1_1), U8.26 (TEST)
unnamed: TP30.1 (1_1), U8.1 (TXD)
unnamed: TP8.1 (1_1), U8.15 (USBD+)
unnamed: TP9.1 (1_1), U8.16 (USBD-)
unnamed: TP6.1 (1_1), U8.20 (VCC)
unnamed: TP5.1 (1_1), U8.4 (VCCIO)
unnamed: TP10.1 (1_1), U8.19 (~RESET)
unnamed: TP51.1 (1_1), U9.1 (ENA)
unnamed: TP54.1 (1_1), U9.4 (ENB)
unnamed: TP52.1 (1_1), U9.2 (FLGA)
unnamed: TP53.1 (1_1), U9.3 (FLGB)
unnamed: TP55.1 (1_1), U9.6 (GND)
unnamed: TP58.1 (1_1), U9.7 (IN)
unnamed: TP57.1 (1_1), U9.8 (OUTA)
unnamed: TP56.1 (1_1), U9.5 (OUTB)
unnamed: R17.1, R44.2, U10.2 (EN1)
unnamed: R43.1, R45.1, U10.4 (EN2)
unnamed: C42.1, U10.9 (SS1)
unnamed: C43.1, U10.7 (SS2)
unnamed: R39.1, R48.2, U11.2 (EN1)
unnamed: R46.1, R47.1, U11.4 (EN2)
unnamed: C46.1, U11.9 (SS1)
unnamed: C44.1, U11.7 (SS2)
SDCARDREADER_N: R38.1, U7.16 (DM)
SDCARDREADER_P: R37.1, U7.15 (DP)
USBIN_N: EMI6.5 (D-), TP91.1 (1_1), U2.30 (USBDM_UP)
USBIN_P: EMI6.6 (D+), TP92.1 (1_1), U2.31 (USBDP_UP)
USBUART_N: R35.1, U6.2 (UD-)
USBUART_P: R36.1, U6.1 (UD+)

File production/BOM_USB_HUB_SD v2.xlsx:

| USB HUB USB | REV2
Reference | Quantity | Value | Manufacturer Part Number | DNP (Do not place)
C2, C8, C28, C32 | 4 | 18p 50V 0402 | C0402C180J5GAC7411
C3, C5, C11, C14, C21, C34, C36 | 7 | 4u7 16V 0402 | GRM155R61A475MEAAD
C4, C6, C7, C9, C10, C12, C13, C15, C17-C20, C22, C24, C29-C31, C33, C35, C47, 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 | 21 | 100n 50V 0402 | CC0402KRX5R9BB104
C16, C41, C49, C50 | 4 | 10u 16V 0603 |  | DNP
C23, C25, C51 | 3 | 10n 1kV 1206 | 1206B103K102CT
C26, C27 | 2 | 10u 16V 0603 | CL10A106KO8NQNC
C37, C38, C40, C45 | 4 | 1u 16V 0402 | 0402X105K160CT
C42-C44, C46 | 4 | 1n 50V 0402 | 0402B102K500CT
D3, D9, D12, D14, D16, D17 | 6 | LED 0603 | SMLD12BN1WT86
D4-D8 | 5 | SP4020-01FTG-C | SP4020-01FTG-C
D10, D11, D13, D15, D18-D20 | 7 | SMBJ5.0A-E3_52 | SMBJ5.0A-E3_52
EMI2-EMI6 | 5 | ECMF02-2AMX6 | ECMF02-2AMX6
F2, F3, F11, F12 | 4 | 1206L150THWR |  | DNP
F4, F5, F7 | 3 | 1206L150THWR | 1206L150THWR
FTG1-FTG3 | 3 | Use only in PCB
J1, J3 | 2 | 67298-4091 | 67298-4091
J2 | 1 | 12402012E212A | 12402012E212A
J4 | 1 | PM2.54-1*10 | PM2.54-1*10
J5 | 1 | MSD-4-A | MSD-4-A
R4, R8, R23, R26, R49 | 5 | 1M 0402 | RC0402JR-071ML
R5-R7, R9, R14-R16, R21, R29, R31-R34 | 13 | 12k 0402 | RC0402FR-0712KL
R12, R13, R17, R35-R39, R43, R46 | 10 | 0R 0402 | FRC0402P000 TS
R18, R19, R22, R24, R40, R42 | 6 | 1k 0402 | RC0402JR-071KL
R20, R44, R45, R47, R48 | 5 | 12k 0402 |  | DNP
R25, R27 | 2 | 5K1 0402 | RC0402FR-075K1L
R28, R30 | 2 | 0R 0805 | RC0805JR-070RL
U1 | 1 | NCP1117ST33T3G | NCP1117ST33T3G
U2, U3 | 2 | USB2514BT-I_M2 | USB2514BT-I_M2
U6 | 1 | CH340K | CH340K
U7 | 1 | GL823K | GL823K
U8 | 1 | FT232RL |  | DNP
U9 | 1 | MIC2026-1YM-TR |  | DNP
U10, U11 | 2 | AP22966DC8-7 | AP22966DC8-7
Y1, Y2 | 2 | TSX-3225_24.0000MF20G-AC3 | TSX-3225_24.0000MF20G-AC3
